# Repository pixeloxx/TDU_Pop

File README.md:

## Tactile Pop

A simple oral electro tactile interface based on this [paper by Kurt Kaczmarek](https://www.sciencedirect.com/science/article/pii/S1026309811001702) and some inspiration from Cthulhu Shield by [Sapien LLC](http://sapienllc.com/). 

The basic setup is a shield for the Arduino Mega board, with an edge connector for attaching TDU electrodes. The Tactile Pop itself uses a PCB, so it is not certified for contact with the mouth: please use it at your own risk! The pop should be coated with a food safe resin, leaving the electrodes exposed. Use gold coating on the electrode PCB for a safer surface coating. 

This repository contains firmware, patterns and Eagle project files for the Tactile Pop TDU. 

Repository layout
----------------
- `Code/` — Arduino sketches and supporting code.
  - `Patterns/` — pattern generator and example patterns (`Patterns.ino`).
  - `Screen/`, `Serial/` — alternative sketches and helpers for serial interface and an attached display. 
- `Electronics/` — Eagle project files and CAM outputs for the controller shield and the the pop TDU pcb. 

Quick start
-----------
1. Open the relevant Arduino sketch from `Code/` in the Arduino IDE .
2. Compile and upload to your compatible microcontroller.
3. Use the `Patterns` sketch or the serial interface to send patterns to the device.

Electrode stimulation 
----------------------

A number of parameters in the pulse patter can be changed, to give a range of intensity and qualities of sensation. Longer pulses will effect Nociceptors (prickly, needle like sensations), while shorter will tend to activate tactile receptors. Some stimulation of taste receptors is also possible.     

The the following parameters can be edited, and fine tuned for each individual electrode. 

PP[] — Pulse Period (microseconds). Total period of one inner pulse (high + low). Unit: µs.
Pp[] — Pulse-on time (microseconds). Time the pin is HIGH during one inner pulse. Unit: µs. 
IN[] — Inner burst count (integer). Number of inner pulses in one inner burst. 
IP[] — Inner burst pause (microseconds). Pause after each inner burst (time between inner bursts). 
ON[] — Outer burst count (integer). Number of inner bursts in one outer burst. 

Sensing Tongue Contact
----------------------

It's possible to sense tongue contact using ADC-capable pins, which is only the first three rows of the TDU. 
 
 ```C#
    const int sensingPins[5][5] = {
      {A1, A2, A3, A4, A5},
      {A6, A7, A8, A9, A10},
      {A11, A12, A13, A14, A15},
      {1, 2, 3, 4, 5},
      {6, 7, 8, 9, 10}
    };
 ```

The example below shows how you can also read a chanel, to check if the tongue is in contact with an electrode.  
 ```C#
    
    int baseLine = 800; 

    bool readSensing(int row, int col) {
      if (row < 0 || row >= 5 || col < 0 || col >= 5) return -1;
      int pin = sensingPins[row][col];
      return analogRead(pin);
        pinMode(pin, OUTPUT);
        digitalWrite(pin, HIGH);
        delayMicroseconds(400);
        pinMode(pin, INPUT);
        int response = analogRead(pin);
        delay(IntensityDelay);
        pinMode(pin, OUTPUT);
        digitalWrite(pin, LOW);
        return (response>baseLine);
    }

 ```

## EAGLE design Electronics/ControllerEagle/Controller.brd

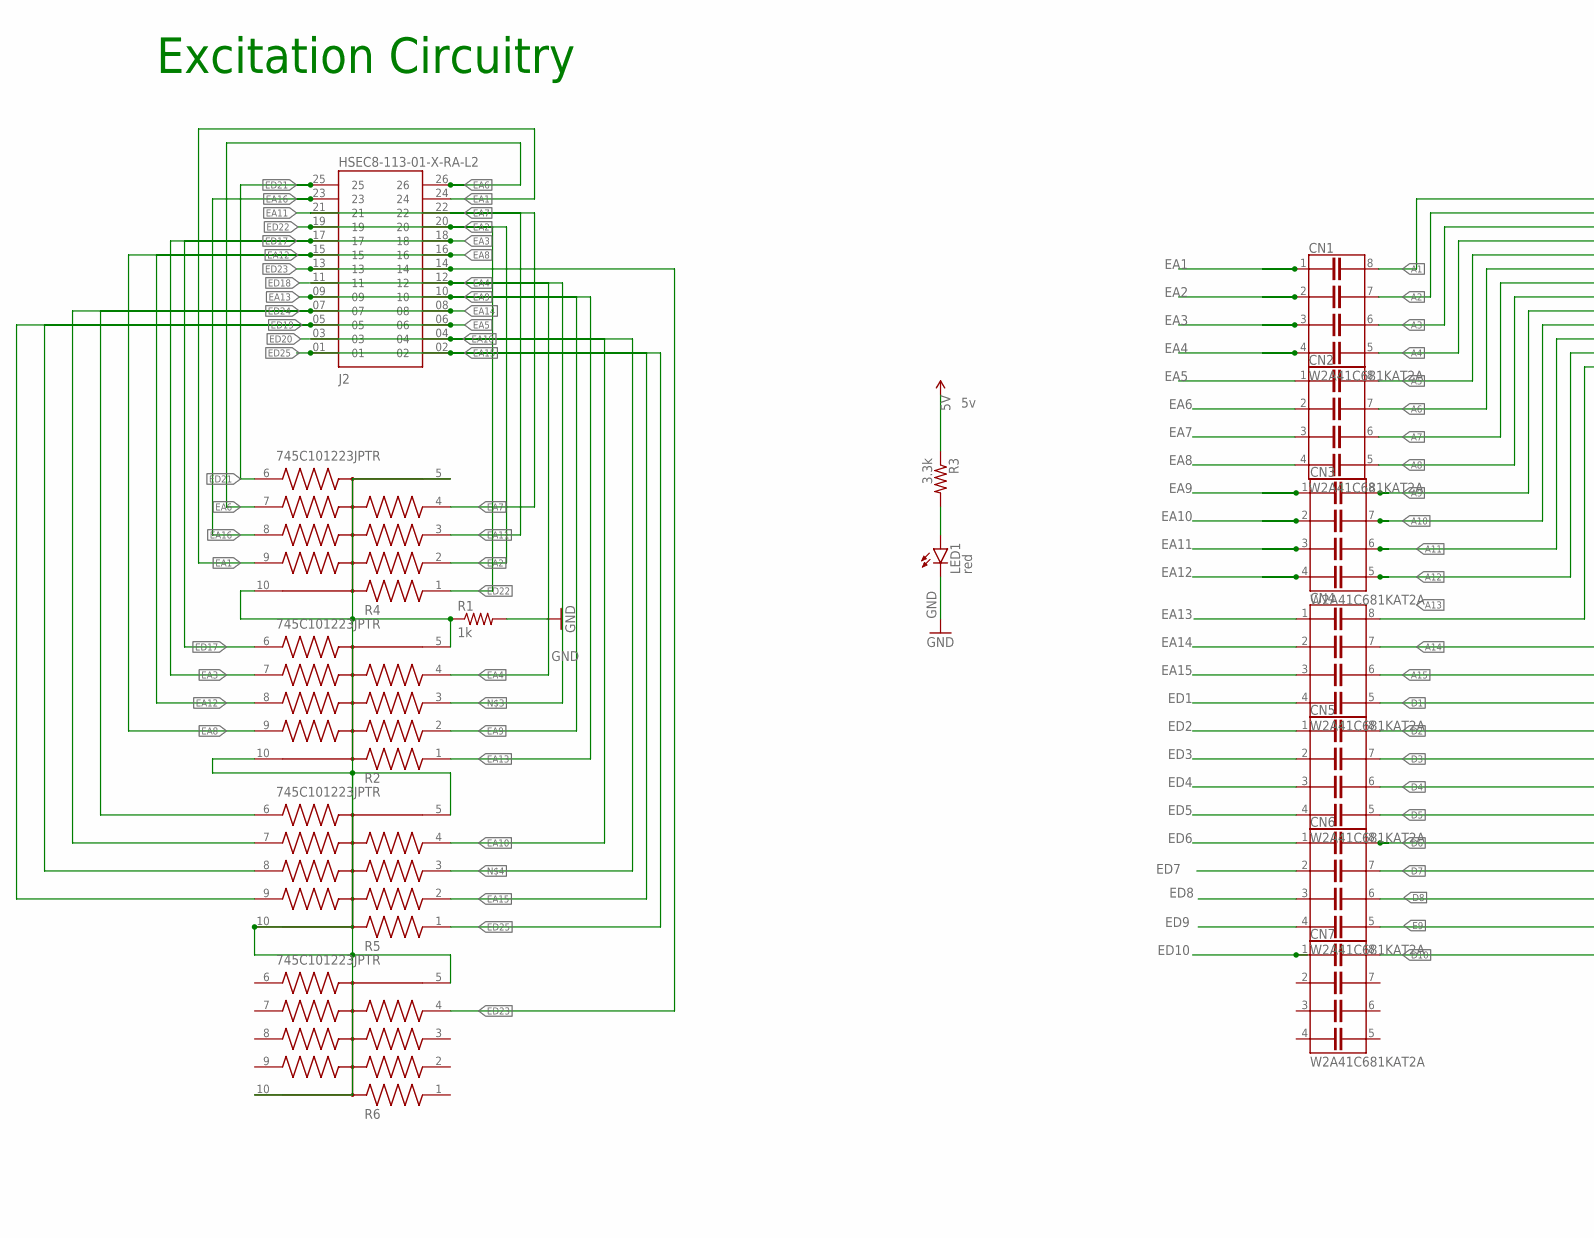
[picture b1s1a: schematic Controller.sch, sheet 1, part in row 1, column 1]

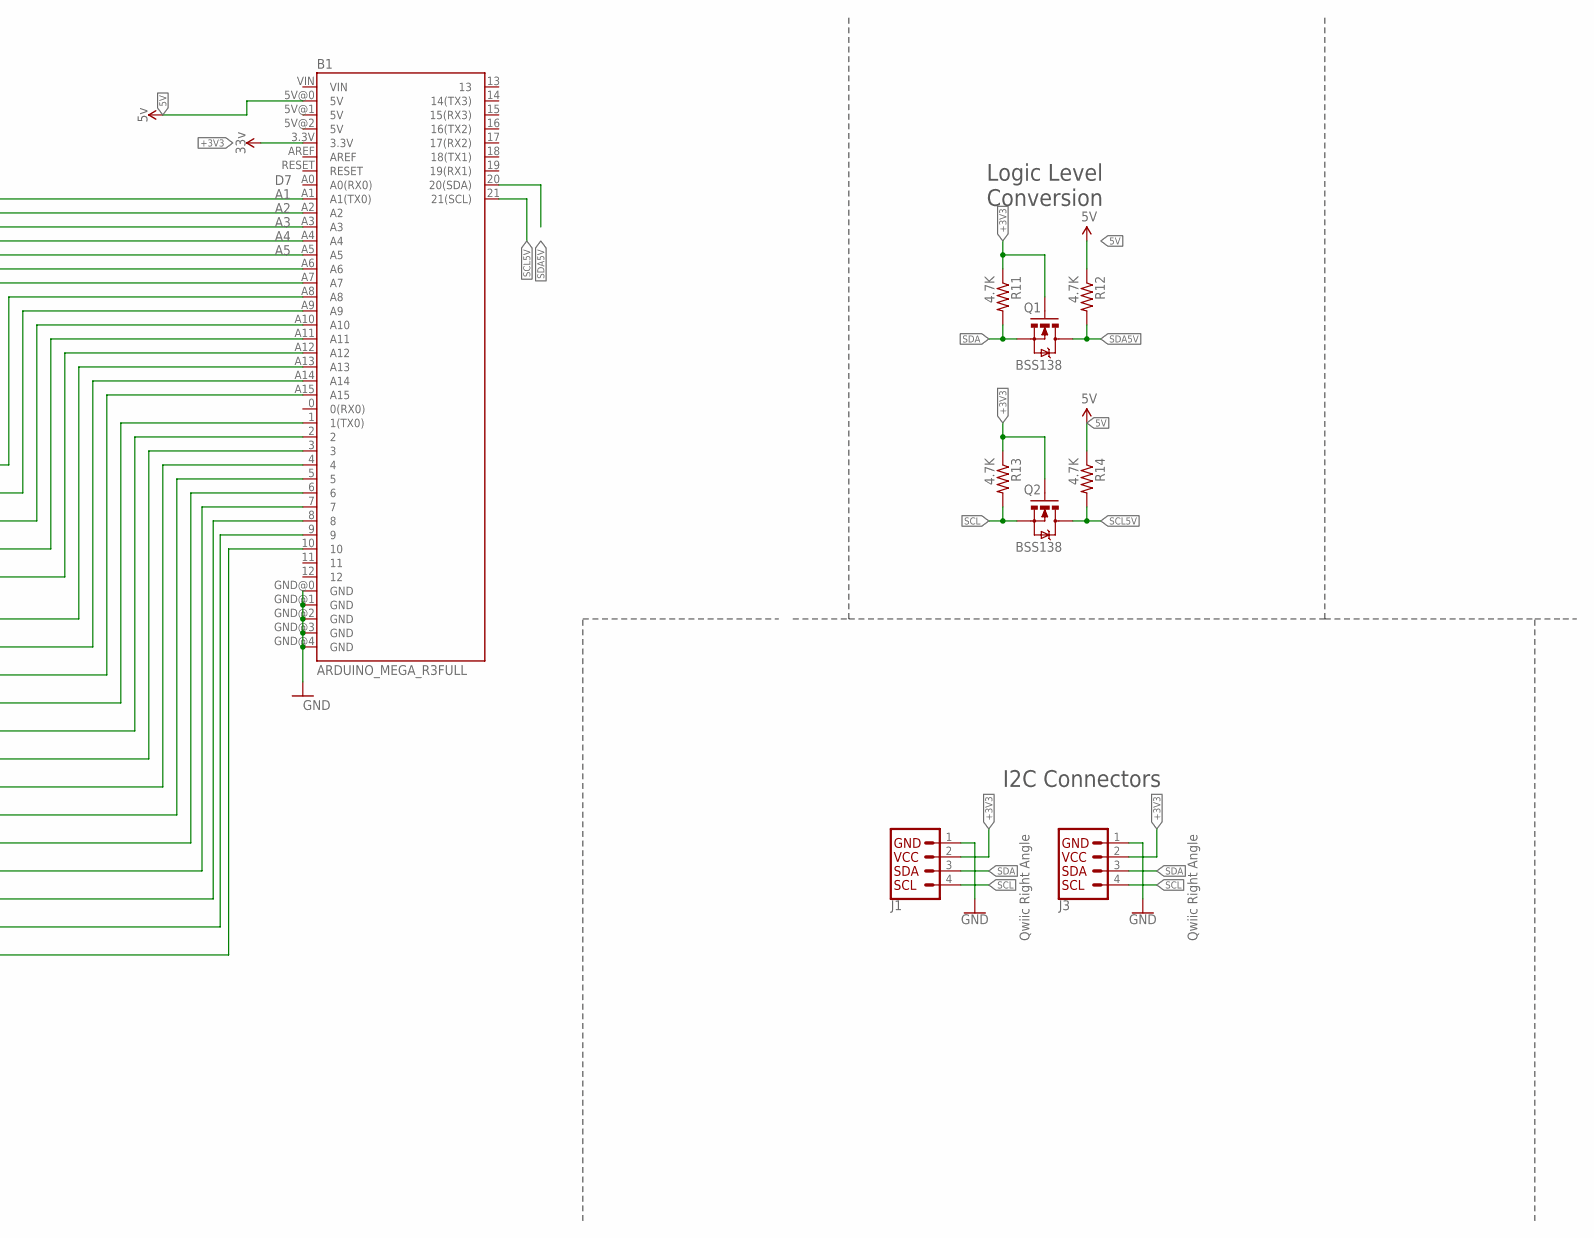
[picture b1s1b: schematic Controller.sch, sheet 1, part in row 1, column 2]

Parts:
B1: ARDUINO_MEGA_R3FULL; ARDUINO_MEGA
CN1, CN2, CN3, CN4, CN5, CN6, CN7: W2A41C681KAT2A; CAPCAXE50P210X130X94-8N
J1, J3: Qwiic Right Angle; 1X04_1MM_RA
J2: HSEC8-113-01-X-RA-L2; SAMTEC_HSEC8-113-01-X-RA-L2
LED1: red; LED-1206
Q1, Q2: BSS138; SOT23-3
R1: 1k; 0402
R2, R4, R5, R6: 745C101223JPTR; RESCAV127P640X310X70-10N
R3: 3.3k; 0402
R11, R12, R13, R14: 4.7K; 0603-RES

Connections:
5V: B1.5V@0 (5V), R3.1, R12.1, R14.1
+3V3: B1.3.3V, J1.2, J3.2, Q1.1 (G), Q2.1 (G), R11.1, R13.1
A1: B1.A1 (A1(TX0)), CN1.8
A2: B1.A2, CN1.7
A3: B1.A3, CN1.6
A4: B1.A4, CN1.5
A5: B1.A5, CN2.8
A6: B1.A6, CN2.7
A7: B1.A7, CN2.6
A8: B1.A8, CN2.5
A9: B1.A9, CN3.8
A10: B1.A10, CN3.7
A11: B1.A11, CN3.6
A12: B1.A12, CN3.5
A13: B1.A13, CN4.8
A14: B1.A14, CN4.7
A15: B1.A15, CN4.6
D1: B1.1 (1(TX0)), CN4.5
D2: B1.2, CN5.8
D3: B1.3, CN5.7
D4: B1.4, CN5.6
D5: B1.5, CN5.5
D6: B1.6, CN6.8
D7: B1.7, CN6.7
D8: B1.8, CN6.6
D10: B1.10, CN7.8
E9: B1.9, CN6.5
EA1: CN1.1, J2.24, R4.9
EA2: CN1.2, J2.20, R4.2
EA3: CN1.3, J2.18, R2.7
EA4: CN1.4, J2.12, R2.4
EA5: CN2.1, J2.06, R5.9
EA6: CN2.2, J2.26, R4.7
EA7: CN2.3, J2.22, R4.4
EA8: CN2.4, J2.16, R2.9
EA9: CN3.1, J2.10, R2.2
EA10: CN3.2, J2.04, R5.4
EA11: CN3.3, J2.21, R4.3
EA12: CN3.4, J2.15, R2.8
EA13: CN4.1, J2.09, R2.1
EA14: CN4.2, J2.08, R5.7
EA15: CN4.3, J2.02, R5.2
EA16: J2.23, R4.8
ED1: CN4.4
ED2: CN5.1
ED3: CN5.2
ED4: CN5.3
ED5: CN5.4
ED6: CN6.1
ED7: CN6.2
ED8: CN6.3
ED9: CN6.4
ED10: CN7.1
ED17: J2.17, R2.6
ED19: J2.05, R5.8
ED21: J2.25, R4.6
ED22: J2.19, R4.1
ED23: J2.13, J2.14, R6.4
ED24: J2.07, R5.6
ED25: J2.01, R5.1
GND: B1.GND@0 (GND), B1.GND@1 (GND), B1.GND@2 (GND), B1.GND@3 (GND), B1.GND@4 (GND), J1.1, J3.1, LED1.C, R1.2
unnamed: LED1.A, R3.2
unnamed: R1.1, R2.5, R2.10, R4.5, R4.10, R5.5, R5.10, R6.5, R6.10
unnamed: J2.11, R2.3
unnamed: J2.03, R5.3
SCL: J1.4, J3.4, Q2.2 (S), R13.2
SCL5V: B1.21 (21(SCL)), Q2.3 (D), R14.2
SDA: J1.3, J3.3, Q1.2 (S), R11.2
SDA5V: B1.20 (20(SDA)), Q1.3 (D), R12.2

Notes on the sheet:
Excitation Circuitry
Logic Level Conversion
I2C Connectors

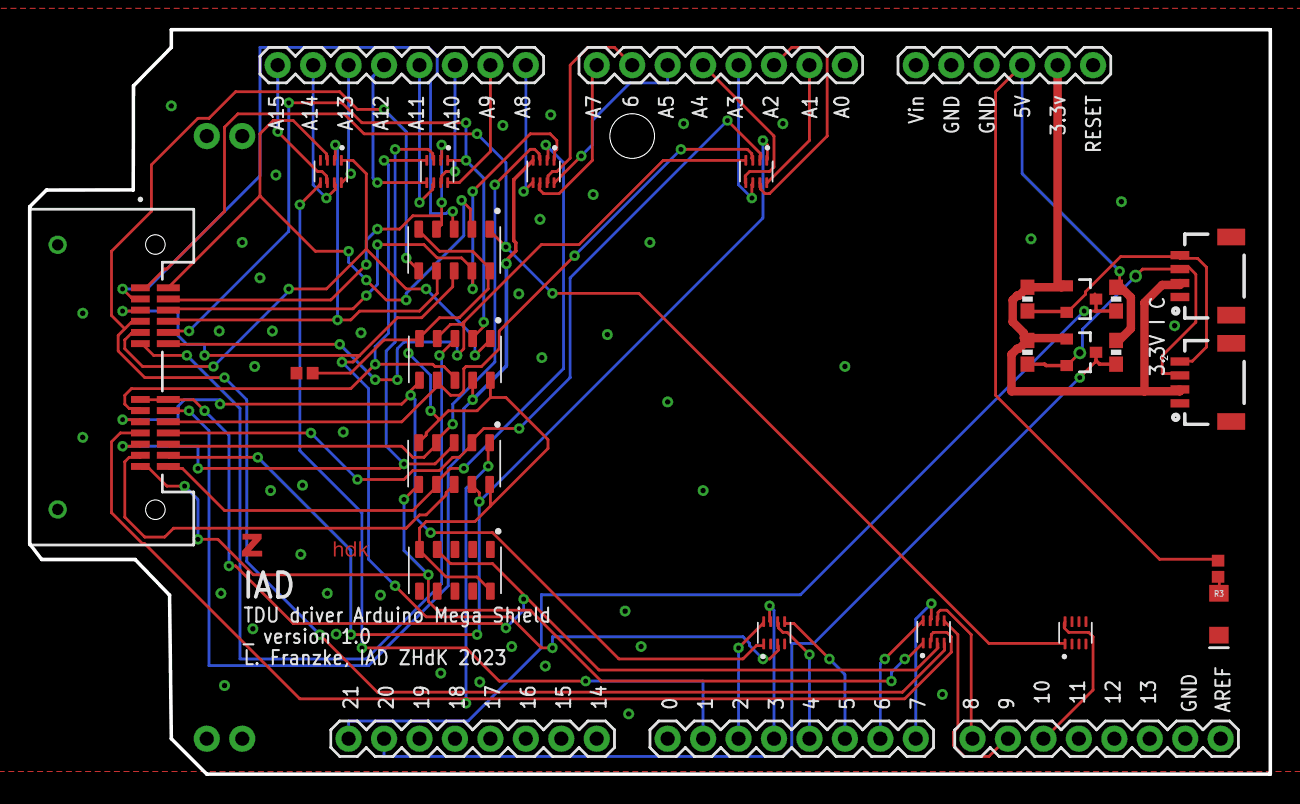
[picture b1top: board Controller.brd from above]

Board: 2 copper layers, 88.9 x 53.3 mm, 25 parts (0 on the bottom side), 59 nets.

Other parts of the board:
U$1: ZHDK_LOGO

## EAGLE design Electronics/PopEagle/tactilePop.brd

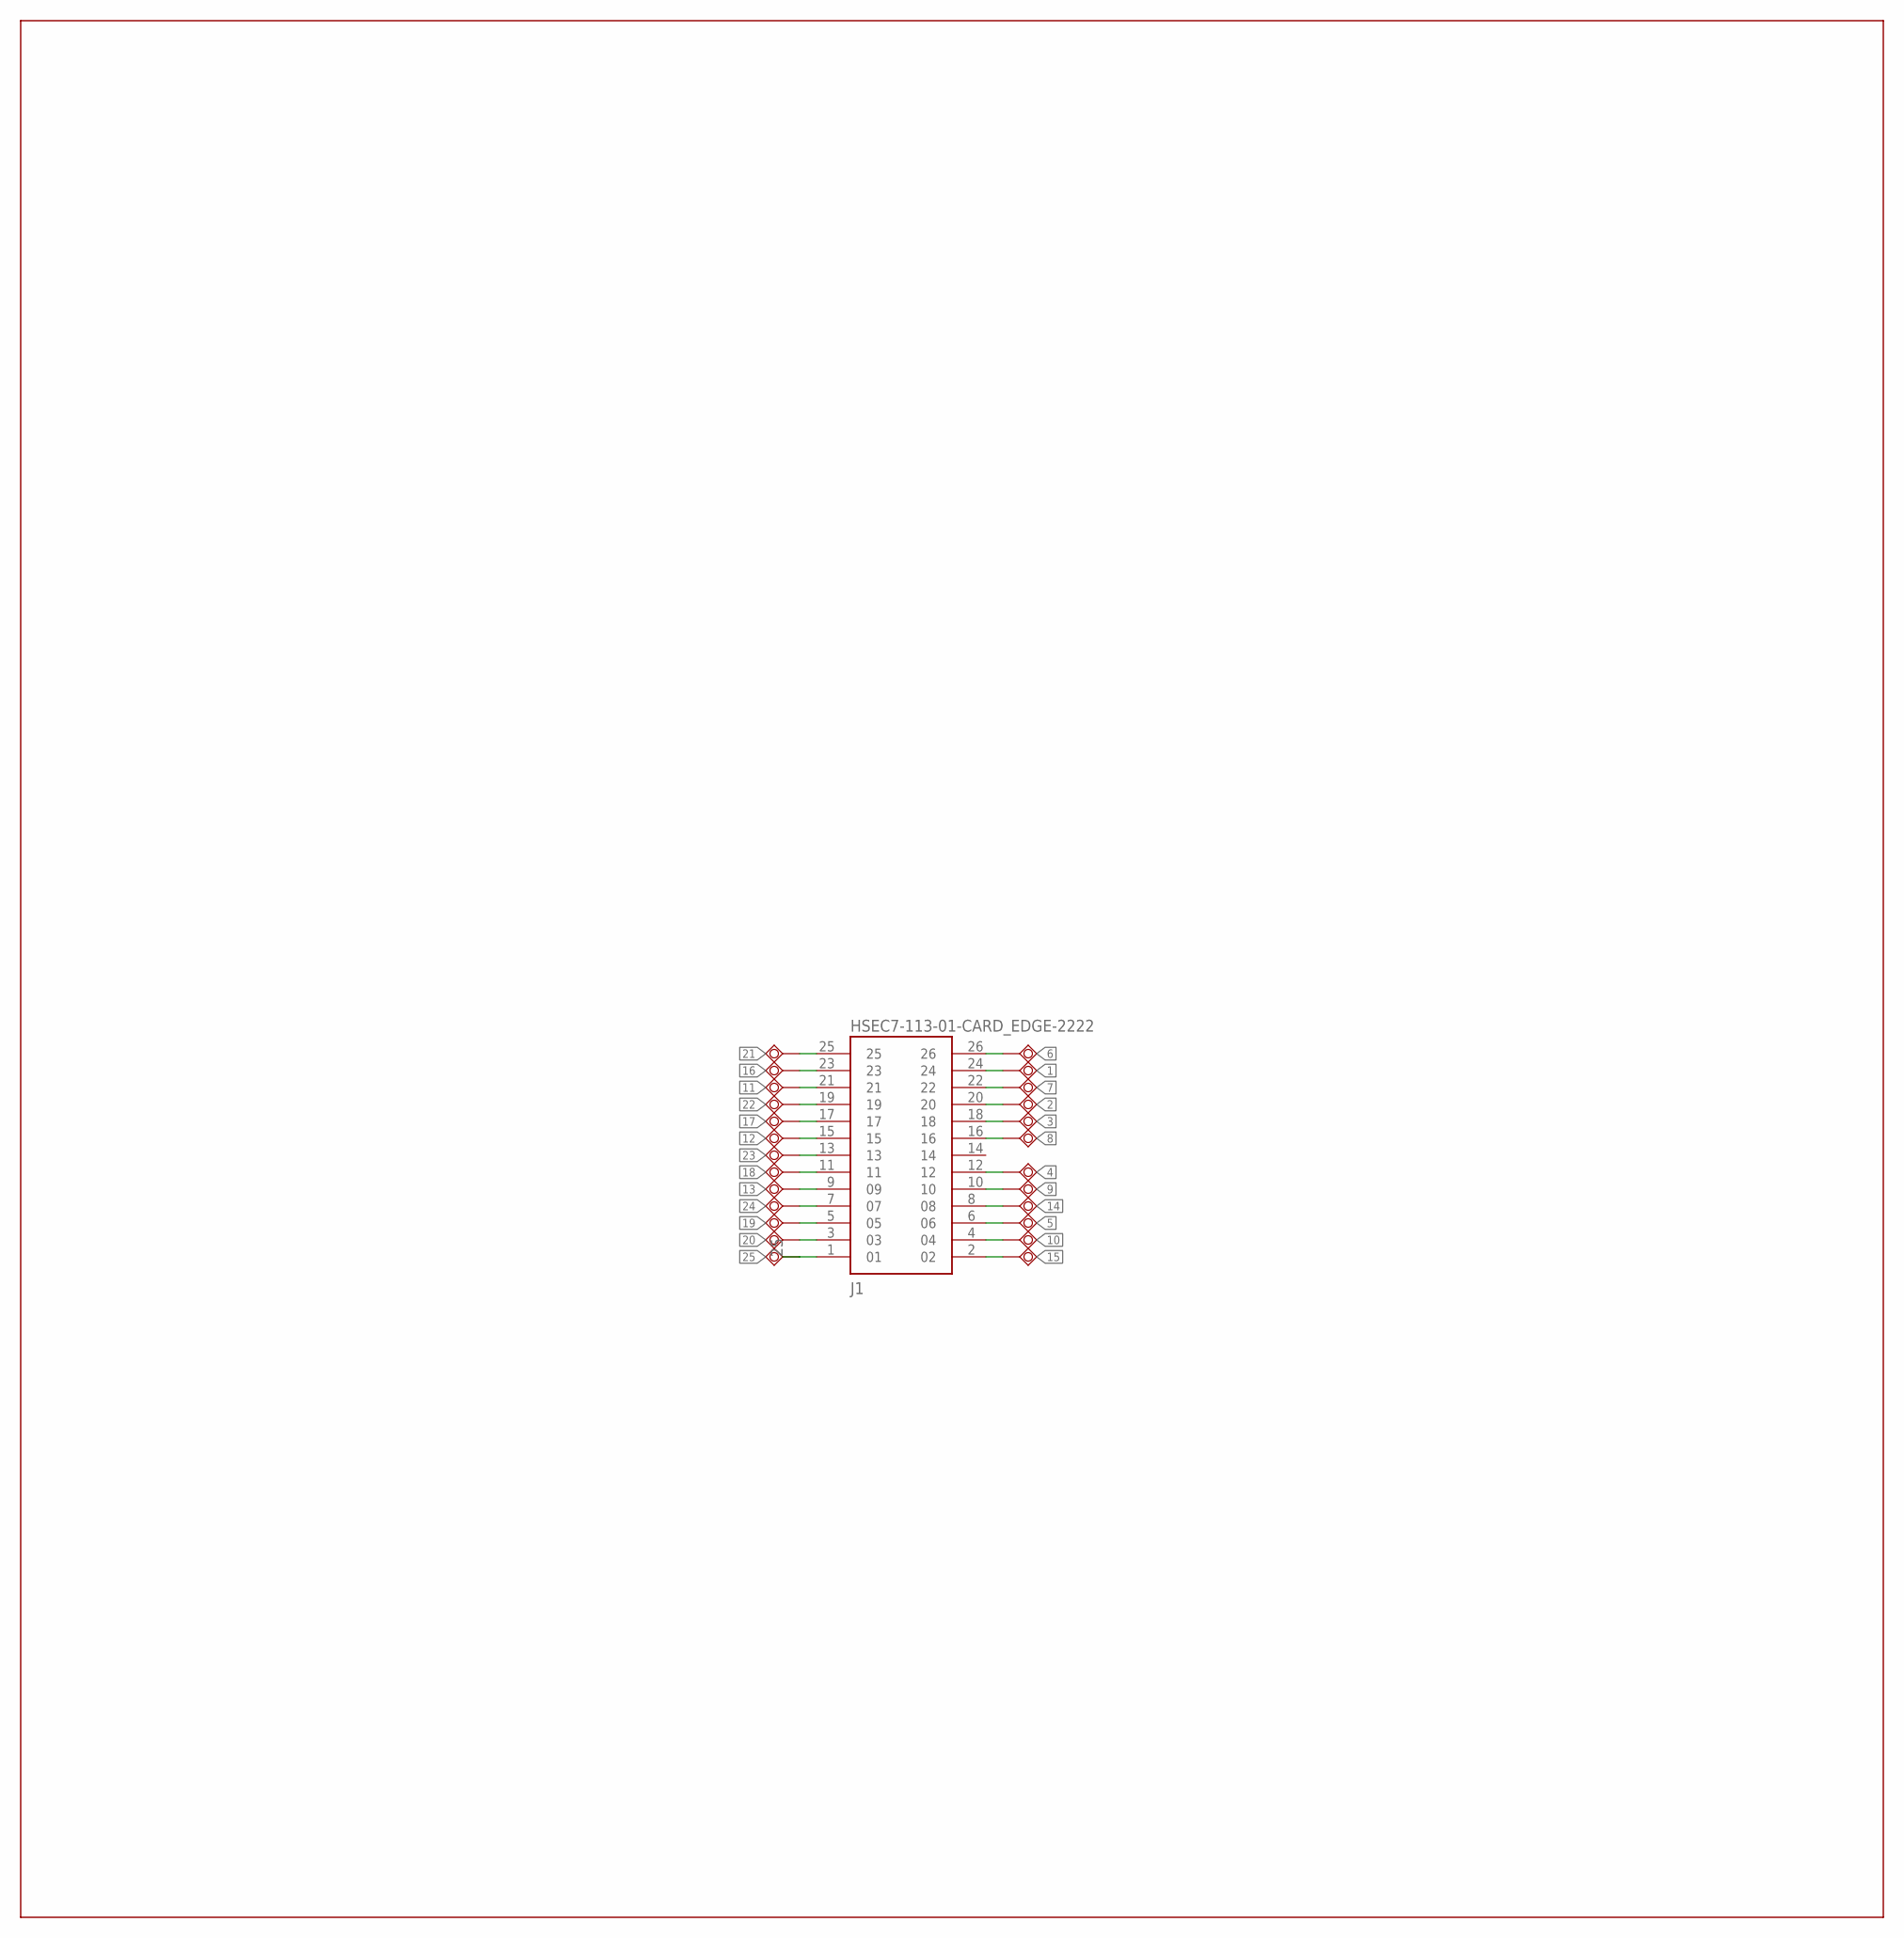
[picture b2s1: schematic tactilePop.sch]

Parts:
1, 2, 3: TESTPAD_TPSQB2,54; TESTPAD_B2,54
J1: HSEC7-113-01-CARD_EDGE-2222; HSEC8-113-01-X-RA-L2
TP1, TP3, TP6, TP7, TP8, TP9, TP10, TP11, TP12, TP13, TP14, TP15, TP16, TP17, TP18, TP19, TP20, TP21, TP22, TP23, TP24, TP25: TESTPAD_TPSQB2,54; TESTPAD_B2,54

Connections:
1: 1.TP, J1.24
2: 2.TP, J1.20
3: 3.TP, J1.18
4: J1.12, TP7.TP
5: J1.6, TP19.TP
6: J1.26, TP1.TP
7: J1.22, TP3.TP
8: J1.16, TP6.TP
9: J1.10, TP8.TP
10: J1.4, TP10.TP
11: J1.21, TP24.TP
12: J1.15, TP21.TP
13: J1.9, TP16.TP
14: J1.8, TP20.TP
15: J1.2, TP11.TP
16: J1.23, TP25.TP
17: J1.17, TP22.TP
18: J1.11, TP17.TP
19: J1.5, TP14.TP
20: J1.3, TP13.TP
21: J1.25, TP9.TP
22: J1.19, TP23.TP
23: J1.13, TP18.TP
24: J1.7, TP15.TP
25: J1.1, TP12.TP

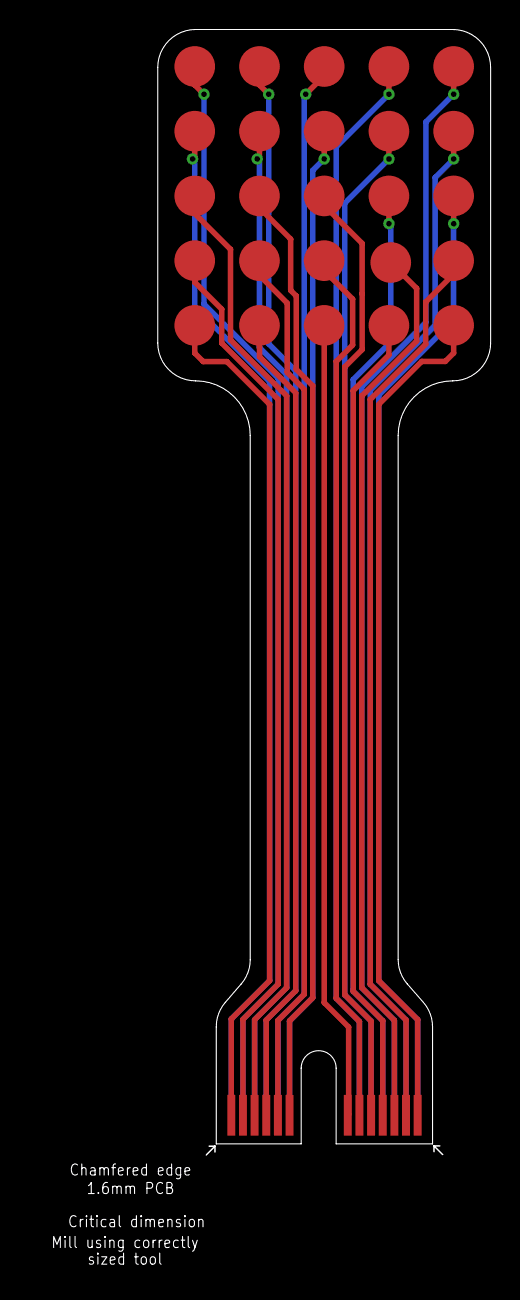
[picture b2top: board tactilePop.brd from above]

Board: 2 copper layers, 22.9 x 77.3 mm, 26 parts (0 on the bottom side), 25 nets.

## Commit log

2026-01-31 Fix typo in README.md for electro tactile interface
2026-05-22 Update README for clarity and safety warnings
    Clarified the description of the Tactile Pop and updated safety warnings regarding its use.

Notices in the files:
parts and their libraries:
SparkFun-LED: Licensing: Creative Commons ShareAlike 4.0 International - https://creativecommons.org/licenses/by-sa/4.0
SparkFun-Aesthetics: Licensing: CC v3.0 Share-Alike You are welcome to use this library for commercial purposes.
